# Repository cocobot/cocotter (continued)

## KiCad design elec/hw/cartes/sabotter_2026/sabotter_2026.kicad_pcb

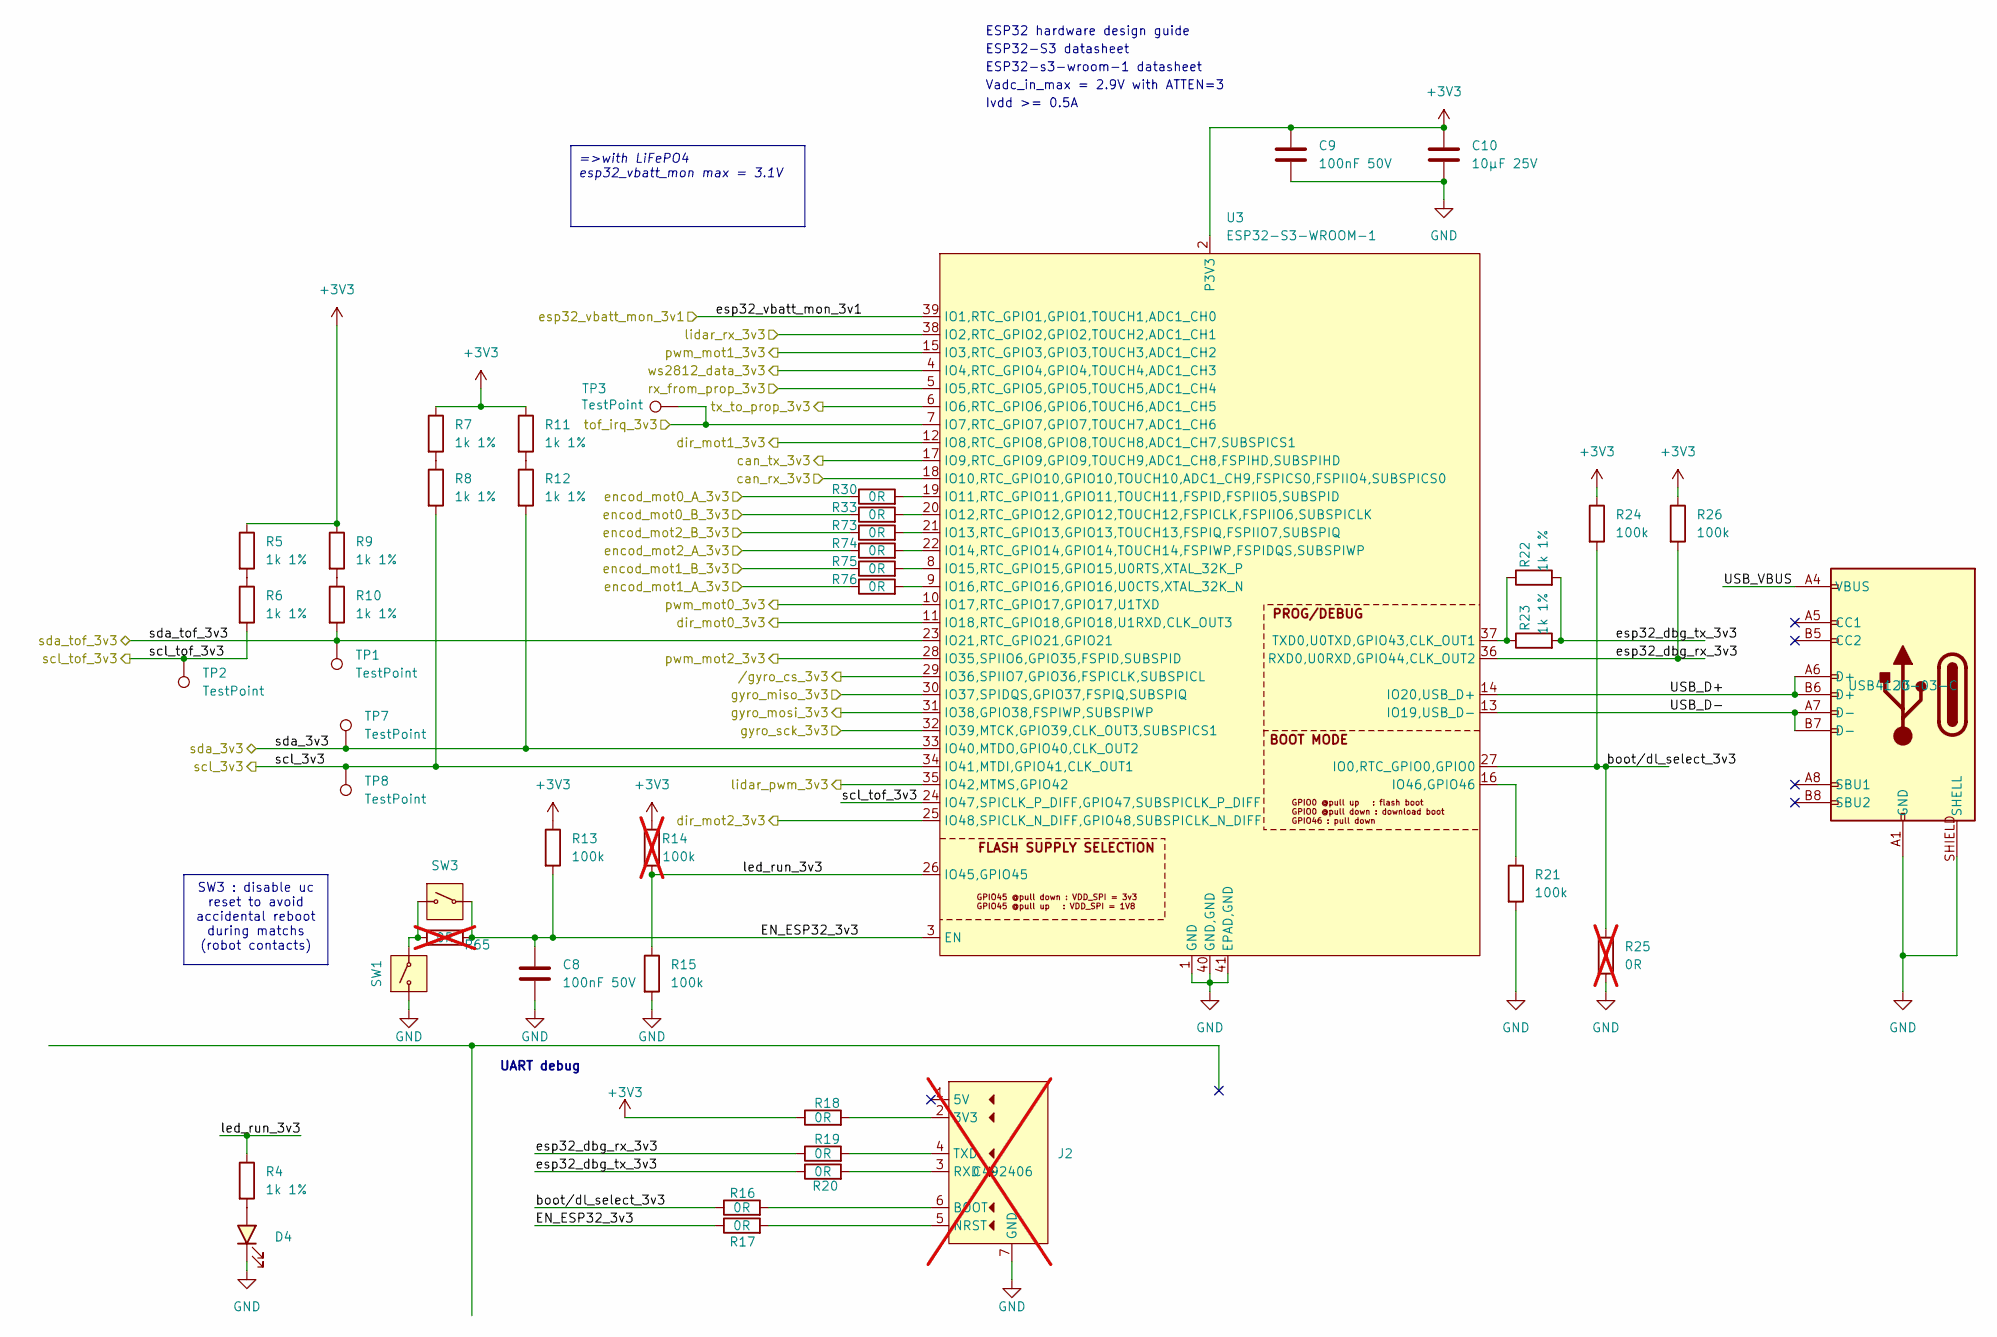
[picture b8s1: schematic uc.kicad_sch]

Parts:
C8, C9: 100nF 50V; C_0603_1608Metric; JLCPCB Part # C14663
C10: 10µF 25V; C_0805_2012Metric; JLCPCB Part # C15850
D4: green, 0603; LED_0603_1608Metric; DIGIKEY_REF 3147-B19Y1UYG-20C000313U1930CT-ND
J2: eps32_uart_programmer; JLCPCB Part # C492406; not fitted
J3: USB4120-03-C; JLCPCB Part # C7450621
R4, R5, R6, R7, R8, R9, R10, R11, R12, R22, R23: 1k 1%; r0603_reflow; mouser 603-RC0603FR-10100KL
R13, R15, R21, R24, R26: 100k; r0603_reflow; mouser 603-RC0603FR-10100KL
R14: 100k; r0603_reflow; mouser 603-RC0603FR-10100KL; not fitted
R16, R17, R18, R19, R20, R30, R33, R73, R74, R75, R76: 0R; r0603_reflow; JLCPCB Part # C431718
R25, R65: 0R; r0603_reflow; JLCPCB Part # C431718; not fitted
SW1: PTS525 SK15 SMTR2 LFS; PTS525; JLCPCB Part # C2689599
SW3: DSIC01LSGER; DIP_SW_SMD-1P; JLCPCB Part # C5370250
TP1, TP2, TP3, TP7, TP8: TestPoint; testpoint-THT-0.5mm
U3: ESP32-S3-WROOM-1; JLCPCB Part # C3013944

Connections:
+3V3: C9.1, C10.1, R5.1, R7.1, R9.1, R11.1, R13.1, R14.1, R18.1, R24.1, R26.1, U3.2 (P3V3); also elsewhere on the board
/interfaces/can_rx_3v3: U3.18 (IO10,RTC_GPIO10,GPIO10,TOUCH10,ADC1_CH9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); also elsewhere on the board
/interfaces/can_tx_3v3: U3.17 (IO9,RTC_GPIO9,GPIO9,TOUCH9,ADC1_CH8,FSP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); also elsewhere on the board
/interfaces/rx_from_prop_3v3: U3.5 (IO5,RTC_GPIO5,GPIO5,TOUCH5,ADC1_CH4); also elsewhere on the board
/interfaces/scl_3v3: R8.2, TP8.1, U3.34 (IO41,MTDI,GPIO41,CLK_OUT1); also elsewhere on the board
/interfaces/sda_3v3: R12.2, TP7.1, U3.33 (IO40,MTDO,GPIO40,CLK_OUT2); also elsewhere on the board
/interfaces/tx_to_prop_3v3: U3.6 (IO6,RTC_GPIO6,GPIO6,TOUCH6,ADC1_CH5); also elsewhere on the board
/interfaces/ws2812_data_3v3: U3.4 (IO4,RTC_GPIO4,GPIO4,TOUCH4,ADC1_CH3); also elsewhere on the board
/motors/DIR_MOT0_3V3: U3.11 (IO18,RTC_GPIO18,GPIO18,U1RXD,CLK_OUT3); also elsewhere on the board
/motors/DIR_MOT1_3V3: U3.12 (IO8,RTC_GPIO8,GPIO8,TOUCH8,ADC1_CH7,SUB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); also elsewhere on the board
/motors/DIR_MOT2_3V3: U3.25 (IO48,SPICLK_N_DIFF,GPIO48,SUBSPICLK_N_D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); also elsewhere on the board
/motors/ENCODER_A_MOT0_3V3: R30.1; also elsewhere on the board
/motors/ENCODER_A_MOT1_3V3: R76.1; also elsewhere on the board
/motors/ENCODER_A_MOT2_3V3: R74.1; also elsewhere on the board
/motors/ENCODER_B_MOT0_3V3: R33.1; also elsewhere on the board
/motors/ENCODER_B_MOT1_3V3: R75.1; also elsewhere on the board
/motors/ENCODER_B_MOT2_3V3: R73.1; also elsewhere on the board
/motors/PWM_MOT0_3V3: U3.10 (IO17,RTC_GPIO17,GPIO17,U1TXD); also elsewhere on the board
/motors/PWM_MOT1_3V3: U3.15 (IO3,RTC_GPIO3,GPIO3,TOUCH3,ADC1_CH2); also elsewhere on the board
/motors/PWM_MOT2_3V3: U3.28 (IO35,SPIIO6,GPIO35,FSPID,SUBSPID); also elsewhere on the board
/motors/tof_irq_3v3: TP3.1, U3.7 (IO7,RTC_GPIO7,GPIO7,TOUCH7,ADC1_CH6); also elsewhere on the board
/scl_tof_3v3: R6.2, TP2.1, U3.24 (IO47,SPICLK_P_DIFF,GPIO47,SUBSPICLK_P_D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); also elsewhere on the board
/sda_tof_3v3: R10.2, TP1.1, U3.23 (IO21,RTC_GPIO21,GPIO21); also elsewhere on the board
/sensors/gyro_miso_3v3: U3.30 (IO37,SPIDQS,GPIO37,FSPIQ,SUBSPIQ); also elsewhere on the board
/sensors/gyro_mosi_3v3: U3.31 (IO38,GPIO38,FSPIWP,SUBSPIWP); also elsewhere on the board
/sensors/gyro_sck_3v3: U3.32 (IO39,MTCK,GPIO39,CLK_OUT3,SUBSPICS1); also elsewhere on the board
/sensors/lidar_pwm_3v3: U3.35 (IO42,MTMS,GPIO42); also elsewhere on the board
/sensors/lidar_rx_3v3: U3.38 (IO2,RTC_GPIO2,GPIO2,TOUCH2,ADC1_CH1); also elsewhere on the board
/sensors//gyro_cs_3v3: U3.29 (IO36,SPIIO7,GPIO36,FSPICLK,SUBSPICL); also elsewhere on the board
/uc/EN_ESP32_3v3: C8.1, R13.2, R17.1, R65.2, SW3.2, U3.3 (EN)
/uc/USB_D+: J3.A6 (D+), J3.B6 (D+), U3.14 (IO20,USB_D+)
/uc/USB_D-: J3.A7 (D-), J3.B7 (D-), U3.13 (IO19,USB_D-)
/uc/USB_VBUS: J3.A4 (VBUS), J3.A9 (VBUS), J3.B4 (VBUS), J3.B9 (VBUS)
/uc/boot/dl_select_3v3: R16.1, R24.2, R25.1, U3.27 (IO0,RTC_GPIO0,GPIO0)
/uc/esp32_dbg_rx_3v3: R19.1, R26.2, U3.36 (RXD0,U0RXD,GPIO44,CLK_OUT2)
/uc/esp32_dbg_tx_3v3: R20.1, R22.2, R23.2
/uc/esp32_vbatt_mon_3v1: U3.39 (IO1,RTC_GPIO1,GPIO1,TOUCH1,ADC1_CH0); also elsewhere on the board
/uc/led_run_3v3: R4.1, R14.2, R15.1, U3.26 (IO45,GPIO45)
GND: C8.2, C9.2, C10.2, D4.C, J2.7 (GND), J3.A1 (GND), J3.A12 (GND), J3.B1 (GND), J3.B12 (GND), J3.SHIELD (SHELL), R15.2, R21.2, R25.2, SW1.A (1), U3.1 (GND), U3.40 (GND,GND), U3.41 (EPAD,GND); also elsewhere on the board
unnamed: D4.A, R4.2
unnamed: J2.2 (3V3), R18.2
unnamed: J2.6 (BOOT), R16.2
unnamed: J2.5 (NRST), R17.2
unnamed: J2.3 (RXD), R20.2
unnamed: J2.4 (TXD), R19.2
unnamed: R5.2, R6.1
unnamed: R7.2, R8.1
unnamed: R9.2, R10.1
unnamed: R11.2, R12.1
unnamed: R65.1, SW1.B (2), SW3.1
unnamed: R30.2, U3.19 (IO11,RTC_GPIO11,GPIO11,TOUCH11,FSPID,FS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)
unnamed: R33.2, U3.20 (IO12,RTC_GPIO12,GPIO12,TOUCH12,FSPICLK,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)
unnamed: R73.2, U3.21 (IO13,RTC_GPIO13,GPIO13,TOUCH13,FSPIQ,FS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)
unnamed: R74.2, U3.22 (IO14,RTC_GPIO14,GPIO14,TOUCH14,FSPIWP,F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)
unnamed: R75.2, U3.8 (IO15,RTC_GPIO15,GPIO15,U0RTS,XTAL_32K_P)
unnamed: R76.2, U3.9 (IO16,RTC_GPIO16,GPIO16,U0CTS,XTAL_32K_N)
unnamed: R21.1, U3.16 (IO46,GPIO46)
unnamed: R22.1, R23.1, U3.37 (TXD0,U0TXD,GPIO43,CLK_OUT1)

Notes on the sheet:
=>with LiFePO4 esp32_vbatt_mon max = 3.1V
SW3 : disable uc reset to avoid accidental reboot during matchs (robot contacts)
UART debug
ESP32-s3-wroom-1 datasheet
Ivdd >= 0.5A
ESP32 hardware design guide
Vadc_in_max = 2.9V with ATTEN=3
ESP32-S3 datasheet

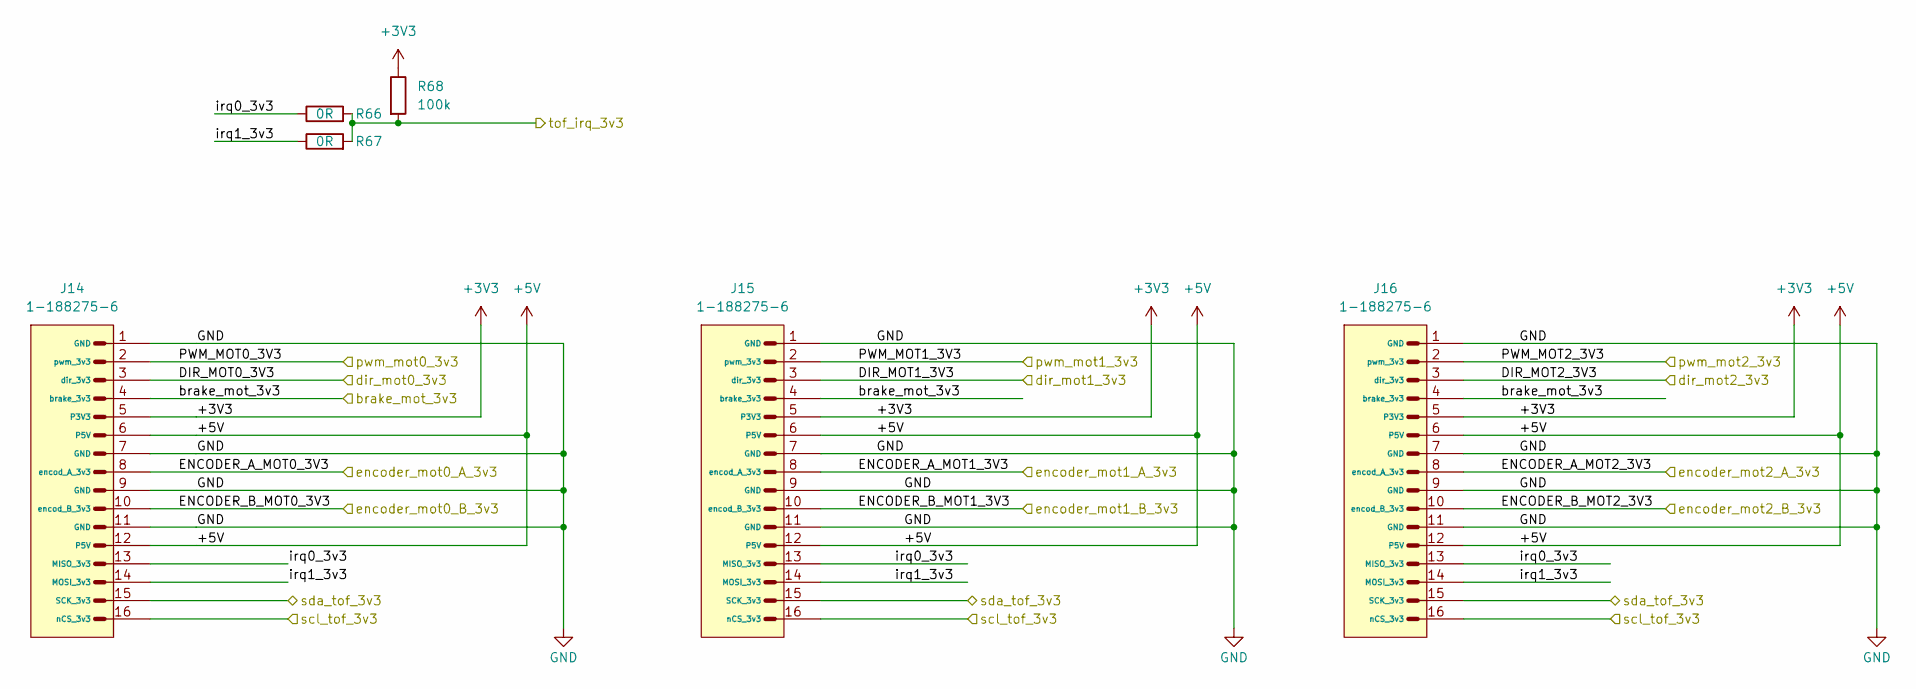
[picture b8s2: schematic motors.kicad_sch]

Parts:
J14, J15, J16: 1-188275-6; JLCPCB Part # C720217
R66, R67: 0R; r0603_reflow; JLCPCB Part # C431718
R68: 100k; r0603_reflow; mouser 603-RC0603FR-10100KL

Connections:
+3V3: J14.5 (P3V3), J15.5 (P3V3), J16.5 (P3V3), R68.1; also elsewhere on the board
+5V: J14.6 (P5V), J14.12 (P5V), J15.6 (P5V), J15.12 (P5V), J16.6 (P5V), J16.12 (P5V); also elsewhere on the board
/brake_mot_3v3: J14.4 (brake_3v3), J15.4 (brake_3v3), J16.4 (brake_3v3); also elsewhere on the board
/motors/DIR_MOT0_3V3: J14.3 (dir_3v3); also elsewhere on the board
/motors/DIR_MOT1_3V3: J15.3 (dir_3v3); also elsewhere on the board
/motors/DIR_MOT2_3V3: J16.3 (dir_3v3); also elsewhere on the board
/motors/ENCODER_A_MOT0_3V3: J14.8 (encod_A_3v3); also elsewhere on the board
/motors/ENCODER_A_MOT1_3V3: J15.8 (encod_A_3v3); also elsewhere on the board
/motors/ENCODER_A_MOT2_3V3: J16.8 (encod_A_3v3); also elsewhere on the board
/motors/ENCODER_B_MOT0_3V3: J14.10 (encod_B_3v3); also elsewhere on the board
/motors/ENCODER_B_MOT1_3V3: J15.10 (encod_B_3v3); also elsewhere on the board
/motors/ENCODER_B_MOT2_3V3: J16.10 (encod_B_3v3); also elsewhere on the board
/motors/PWM_MOT0_3V3: J14.2 (pwm_3v3); also elsewhere on the board
/motors/PWM_MOT1_3V3: J15.2 (pwm_3v3); also elsewhere on the board
/motors/PWM_MOT2_3V3: J16.2 (pwm_3v3); also elsewhere on the board
/motors/irq0_3v3: J14.13 (MISO_3v3), J15.13 (MISO_3v3), J16.13 (MISO_3v3), R66.1
/motors/irq1_3v3: J14.14 (MOSI_3v3), J15.14 (MOSI_3v3), J16.14 (MOSI_3v3), R67.1
/motors/tof_irq_3v3: R66.2, R67.2, R68.2; also elsewhere on the board
/scl_tof_3v3: J14.16 (nCS_3v3), J15.16 (nCS_3v3), J16.16 (nCS_3v3); also elsewhere on the board
/sda_tof_3v3: J14.15 (SCK_3v3), J15.15 (SCK_3v3), J16.15 (SCK_3v3); also elsewhere on the board
GND: J14.1 (GND), J14.7 (GND), J14.9 (GND), J14.11 (GND), J15.1 (GND), J15.7 (GND), J15.9 (GND), J15.11 (GND), J16.1 (GND), J16.7 (GND), J16.9 (GND), J16.11 (GND); also elsewhere on the board

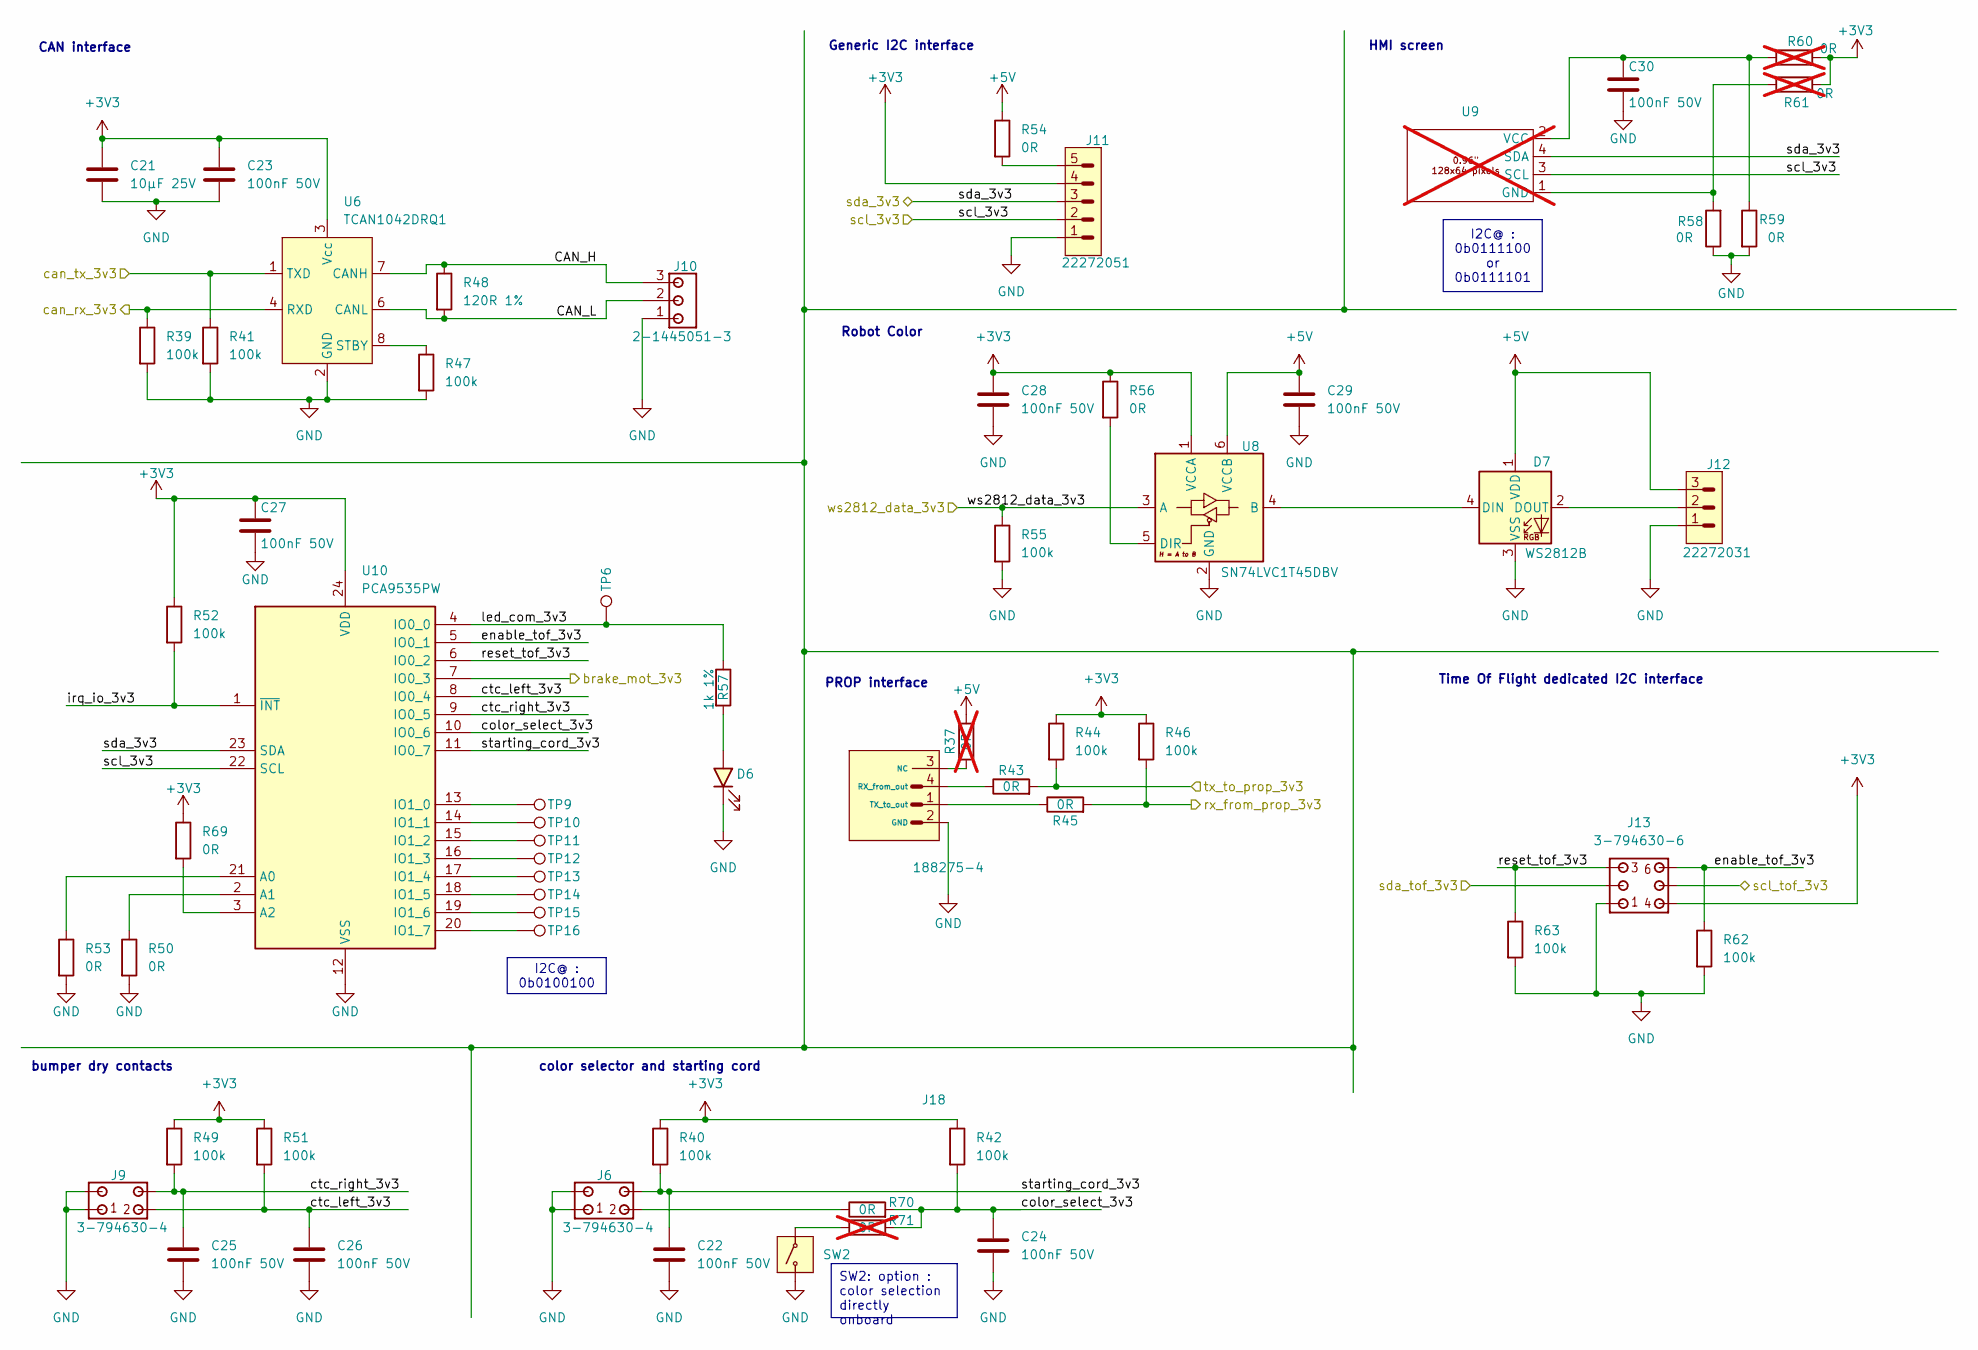
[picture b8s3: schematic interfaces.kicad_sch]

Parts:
C21: 10µF 25V; C_0805_2012Metric; JLCPCB Part # C15850
C22, C23, C24, C25, C26, C27, C28, C29, C30: 100nF 50V; C_0603_1608Metric; JLCPCB Part # C14663
D6: green, 0603; LED_0603_1608Metric; DIGIKEY_REF 3147-B19Y1UYG-20C000313U1930CT-ND
D7: WS2812B; LED_WS2812B_PLCC4_5.0x5.0mm_P3.2mm; JLCPCB Part # C2843785
J6, J9: 3-794630-4; JLCPCB Part # C5164688
J10: 2-1445051-3; JLCPCB Part # C17473329
J11: 22272051; JLCPCB Part # C585785
J12: 22272031; JLCPCB Part # C471416
J13: 3-794630-6; JLCPCB Part # C305795
J18: 188275-4; JLCPCB Part # C720206
R37, R60, R61, R71: 0R; r0603_reflow; JLCPCB Part # C431718; not fitted
R39, R40, R41, R42, R44, R46, R47, R49, R51, R52, R55, R62, R63: 100k; r0603_reflow; mouser 603-RC0603FR-10100KL
R43, R45, R50, R53, R54, R56, R58, R59, R69, R70: 0R; r0603_reflow; JLCPCB Part # C431718
R48: 120R 1%; r1206_reflow; JLCPCB Part # C17909
R57: 1k 1%; r0603_reflow; mouser 603-RC0603FR-10100KL
SW2: DSIC01LSGER; DIP_SW_SMD-1P; JLCPCB Part # C5370250
TP6, TP9, TP10, TP11, TP12, TP13, TP14, TP15, TP16: TestPoint; testpoint-THT-0.5mm
U6: TCAN1042DRQ1; D0008A; JLCPCB Part # C118837
U8: SN74LVC1T45DBV; SOT-23-6; JLCPCB Part # C7843
U9: OLED_0.96inch; not fitted
U10: PCA9535PW; TSSOP-24_4.4x7.8mm_P0.65mm; JLCPCB Part # C42420616

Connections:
+3V3: C21.1, C23.1, C27.1, C28.1, J11.4, J13.4, R40.1, R42.1, R44.1, R46.1, R49.1, R51.1, R52.1, R56.1, R60.2, R61.2, R69.1, U6.3 (Vcc), U8.1 (VCCA), U10.24 (VDD); also elsewhere on the board
+5V: C29.1, D7.1 (VDD), J12.3, R37.2, R54.1, U8.6 (VCCB); also elsewhere on the board
/brake_mot_3v3: U10.7 (IO0_3); also elsewhere on the board
/interfaces/CAN_H: J10.3, R48.1, U6.7 (CANH)
/interfaces/CAN_L: J10.2, R48.2, U6.6 (CANL)
/interfaces/can_rx_3v3: R39.1, U6.4 (RXD); also elsewhere on the board
/interfaces/can_tx_3v3: R41.1, U6.1 (TXD); also elsewhere on the board
/interfaces/color_select_3v3: C24.1, R42.2, R70.2, R71.2, U10.10 (IO0_6)
/interfaces/ctc_left_3v3: C26.1, J9.2, R51.2, U10.8 (IO0_4)
/interfaces/ctc_right_3v3: C25.1, J9.4, R49.2, U10.9 (IO0_5)
/interfaces/enable_tof_3v3: J13.6, R62.1, U10.5 (IO0_1)
/interfaces/irq_io_3v3: R52.2, U10.1 (~INT)
/interfaces/led_com_3v3: R57.1, TP6.1, U10.4 (IO0_0)
/interfaces/reset_tof_3v3: J13.3, R63.1, U10.6 (IO0_2)
/interfaces/rx_from_prop_3v3: R45.2, R46.2; also elsewhere on the board
/interfaces/scl_3v3: J11.2, U9.3 (SCL), U10.22 (SCL); also elsewhere on the board
/interfaces/sda_3v3: J11.3, U9.4 (SDA), U10.23 (SDA); also elsewhere on the board
/interfaces/starting_cord_3v3: C22.1, J6.4, R40.2, U10.11 (IO0_7)
/interfaces/tx_to_prop_3v3: R43.2, R44.2; also elsewhere on the board
/interfaces/ws2812_data_3v3: R55.1, U8.3 (A); also elsewhere on the board
/scl_tof_3v3: J13.5; also elsewhere on the board
/sda_tof_3v3: J13.2; also elsewhere on the board
GND: C21.2, C22.2, C23.2, C24.2, C25.2, C26.2, C27.2, C28.2, C29.2, C30.2, D6.C, D7.3 (VSS), J6.1, J6.3, J9.1, J9.3, J10.1, J11.1, J12.1, J13.1, J18.2 (GND), R39.2, R41.2, R47.2, R50.2, R53.2, R55.2, R58.1, R59.2, R62.2, R63.2, SW2.1, U6.2 (GND), U8.2 (GND), U10.12 (VSS); also elsewhere on the board
unnamed: D6.A, R57.2
unnamed: D7.4 (DIN), U8.4 (B)
unnamed: D7.2 (DOUT), J12.2
unnamed: J6.2, R70.1
unnamed: J11.5, R54.2
unnamed: J18.3 (NC), R37.1
unnamed: J18.4 (RX_from_out), R43.1
unnamed: J18.1 (TX_to_out), R45.1
unnamed: R71.1, SW2.2
unnamed: R47.1, U6.8 (STBY)
unnamed: R56.2, U8.5 (DIR)
unnamed: R58.2, R61.1, U9.1 (GND)
unnamed: C30.1, R59.1, R60.1, U9.2 (VCC)
unnamed: R53.1, U10.21 (A0)
unnamed: R50.1, U10.2 (A1)
unnamed: R69.2, U10.3 (A2)
unnamed: TP9.1, U10.13 (IO1_0)
unnamed: TP10.1, U10.14 (IO1_1)
unnamed: TP11.1, U10.15 (IO1_2)
unnamed: TP12.1, U10.16 (IO1_3)
unnamed: TP13.1, U10.17 (IO1_4)
unnamed: TP14.1, U10.18 (IO1_5)
unnamed: TP15.1, U10.19 (IO1_6)
unnamed: TP16.1, U10.20 (IO1_7)

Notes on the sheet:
I2C@ : 0b0111100 or 0b0111101
SW2: option : color selection directly onboard
I2C@ : 0b0100100
CAN interface
Robot Color
HMI screen
PROP interface
bumper dry contacts
Generic I2C interface
color selector and starting cord
Time Of Flight dedicated I2C interface

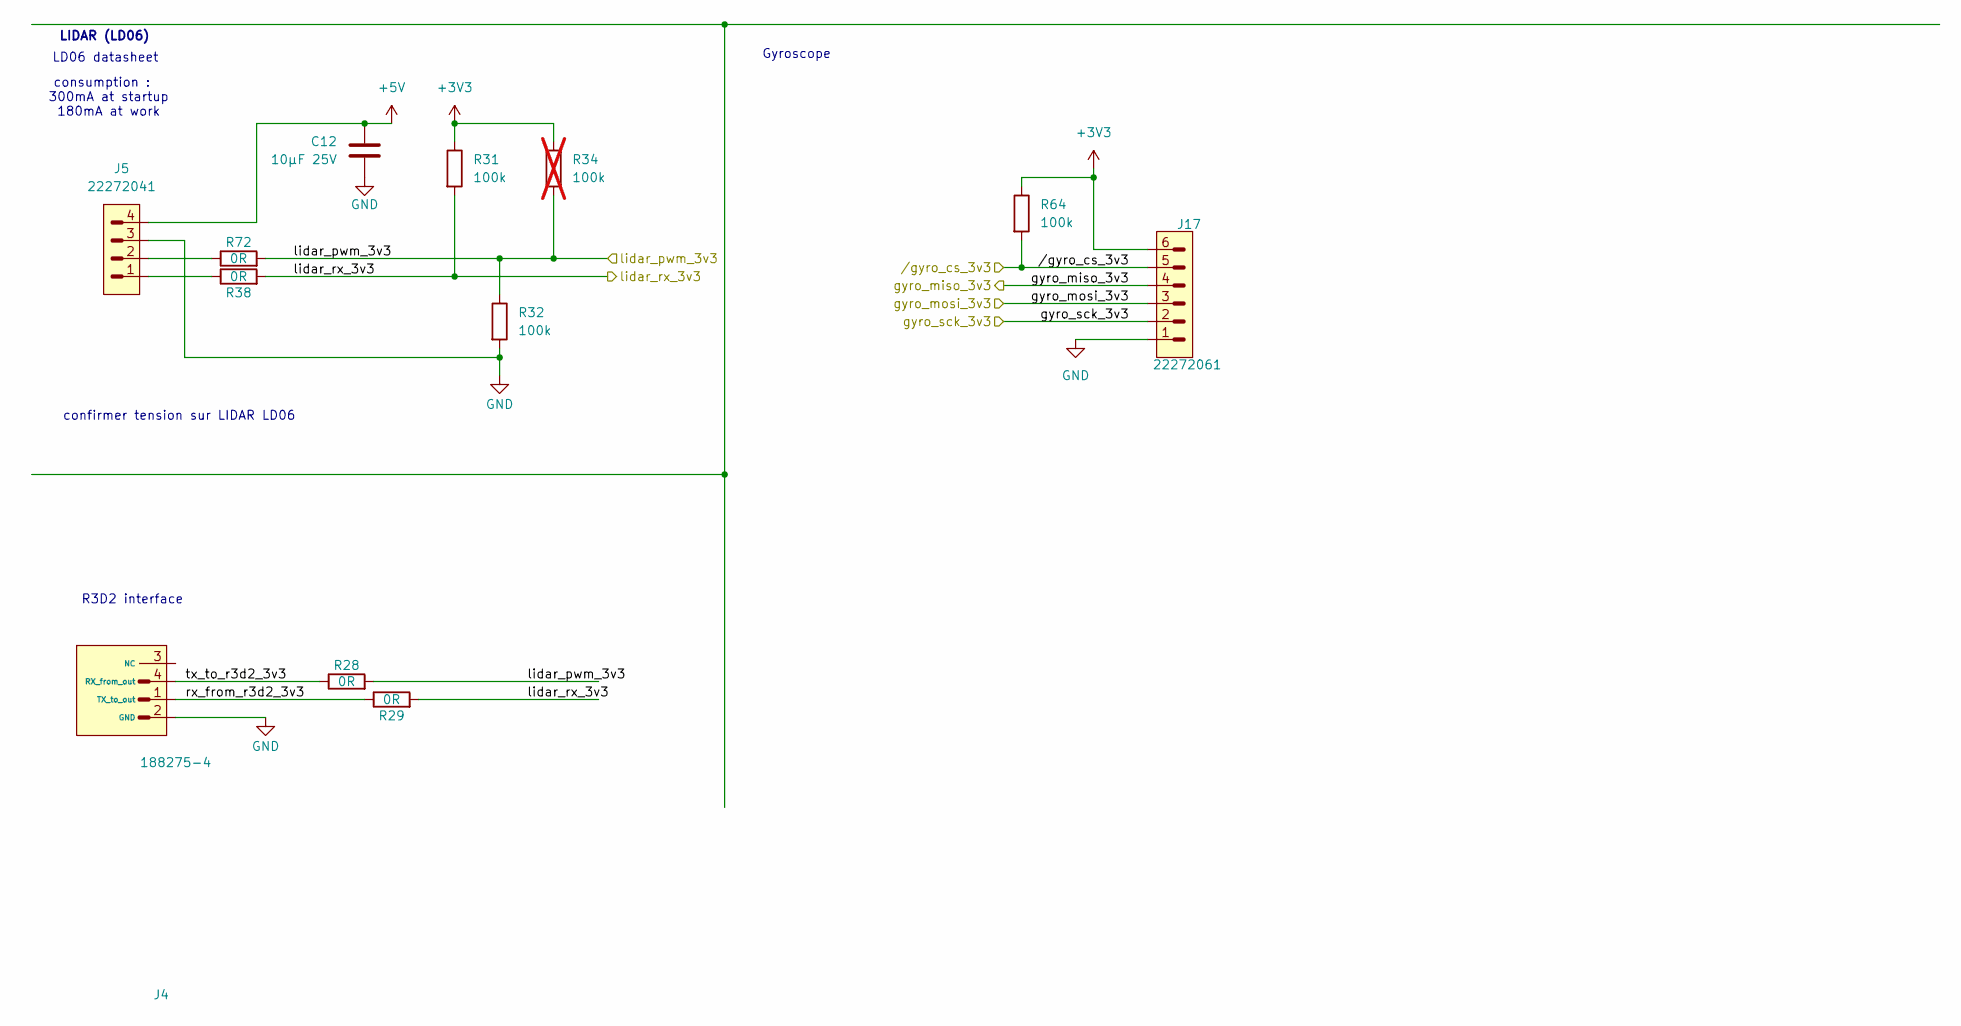
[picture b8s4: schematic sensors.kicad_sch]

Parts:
C12: 10µF 25V; C_0805_2012Metric; JLCPCB Part # C15850
J4: 188275-4; JLCPCB Part # C720206
J5: 22272041; JLCPCB Part # C504991
J17: 22272061; JLCPCB Part # C504992
R28, R29, R38, R72: 0R; r0603_reflow; JLCPCB Part # C431718
R31, R32, R64: 100k; r0603_reflow; mouser 603-RC0603FR-10100KL
R34: 100k; r0603_reflow; mouser 603-RC0603FR-10100KL; not fitted

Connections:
+3V3: J17.6, R31.1, R34.1, R64.1; also elsewhere on the board
+5V: C12.1, J5.4; also elsewhere on the board
/sensors/gyro_miso_3v3: J17.4; also elsewhere on the board
/sensors/gyro_mosi_3v3: J17.3; also elsewhere on the board
/sensors/gyro_sck_3v3: J17.2; also elsewhere on the board
/sensors/lidar_pwm_3v3: R28.2, R32.1, R34.2, R72.2; also elsewhere on the board
/sensors/lidar_rx_3v3: R29.2, R31.2, R38.2; also elsewhere on the board
/sensors/rx_from_r3d2_3v3: J4.1 (TX_to_out), R29.1
/sensors/tx_to_r3d2_3v3: J4.4 (RX_from_out), R28.1
/sensors//gyro_cs_3v3: J17.5, R64.2; also elsewhere on the board
GND: C12.2, J4.2 (GND), J5.3, J17.1, R32.2; also elsewhere on the board
unnamed: J5.1, R38.1
unnamed: J5.2, R72.1

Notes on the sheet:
R3D2 interface
consumption : 300mA at startup 180mA at work
LIDAR (LD06)
Gyroscope
LD06 datasheet
confirmer tension sur LIDAR LD06

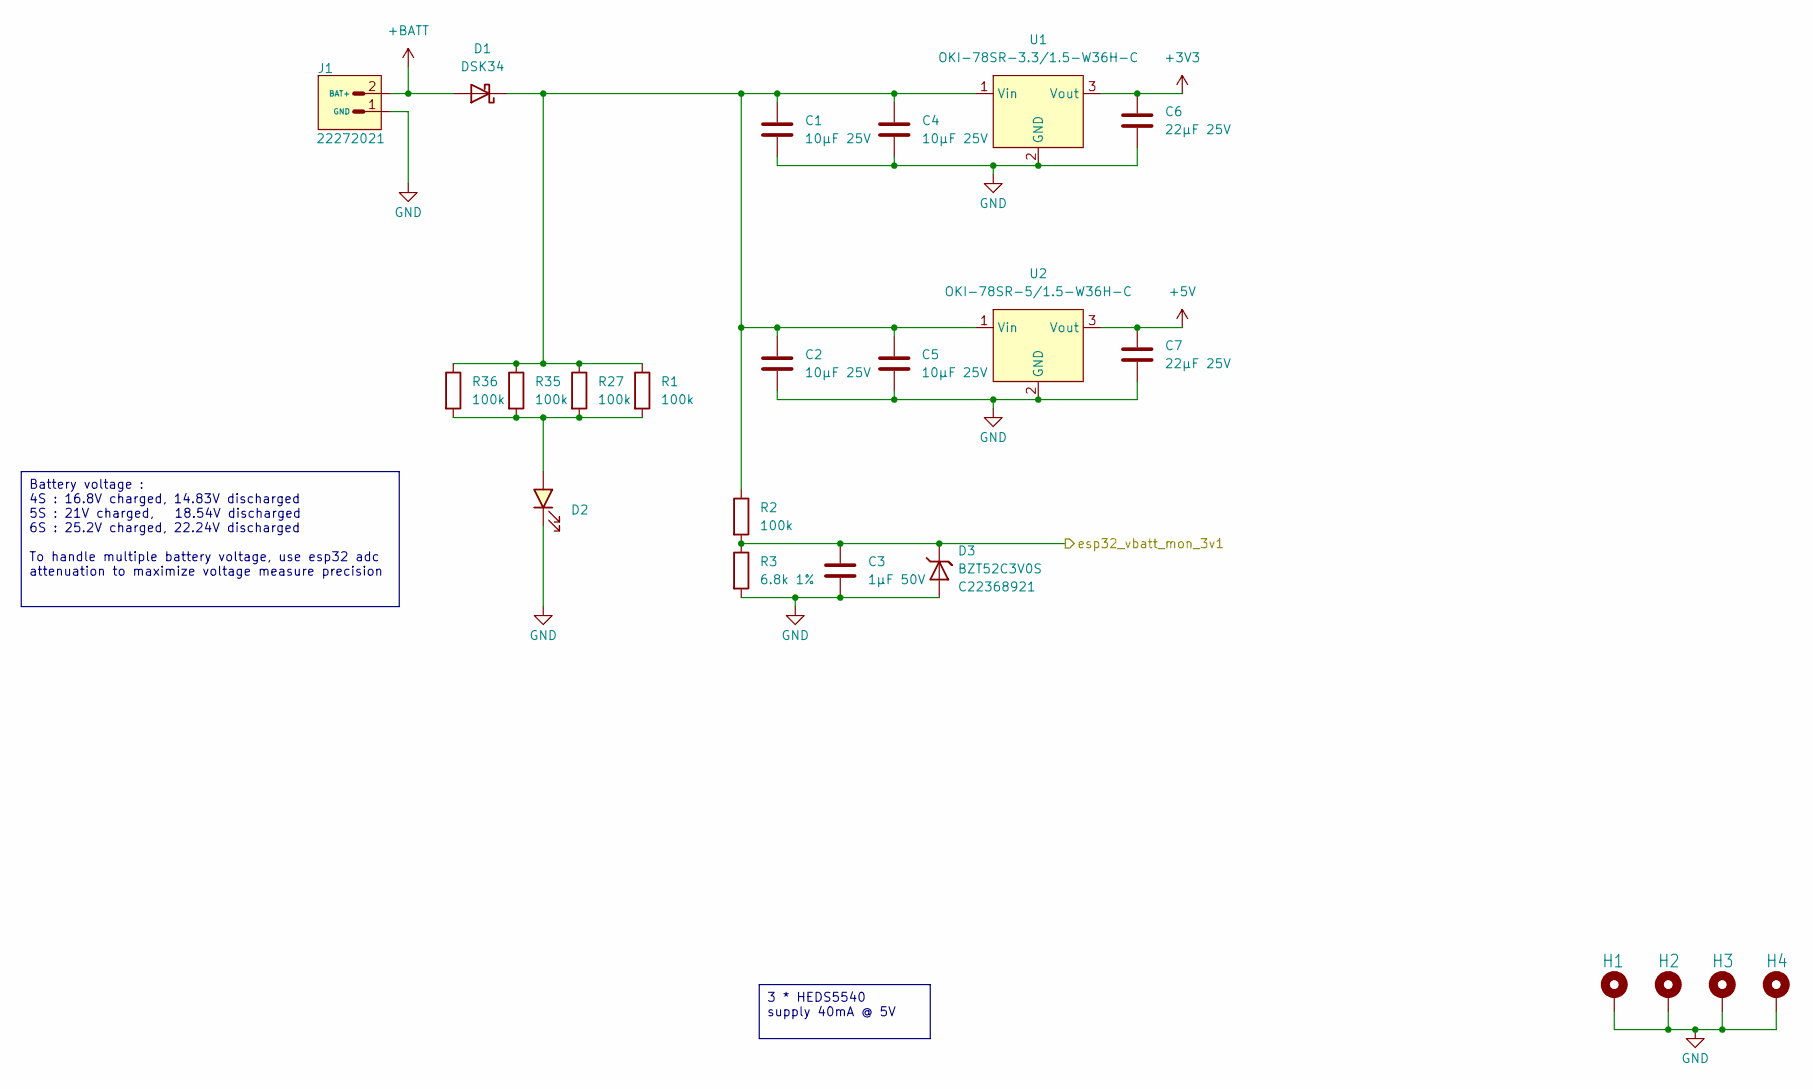
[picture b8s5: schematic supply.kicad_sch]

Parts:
C1, C2, C4, C5: 10µF 25V; C_0805_2012Metric; JLCPCB Part # C15850
C3: 1µF 50V; C_0805_2012Metric; JLCPCB Part # C28323
C6, C7: 22µF 25V; C_1206_3216Metric; JLCPCB Part # C2918511
D1: DSK34; D_SOD-123; JLCPCB Part # C727076
D2: green, 0603; LED_0603_1608Metric; DIGIKEY_REF 3147-B19Y1UYG-20C000313U1930CT-ND
D3: BZT52C3V0S; SOD-323; JLCPCB Part # C22368921
H1, H2, H3, H4: MOUNT-PAD-ROUND3.3; MountingHole_3.2mm_M3_Pad_Via
J1: 22272021; JLCPCB Part # C293316
R1, R2, R27, R35, R36: 100k; r0603_reflow; mouser 603-RC0603FR-10100KL
R3: 6.8k 1%; r0603_reflow; JLCPCB Part # C23212
U1: OKI-78SR-3.3/1.5-W36H-C; OKI78SR-H
U2: OKI-78SR-5/1.5-W36H-C; OKI78SR-H

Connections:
+3V3: C6.1, U1.3 (Vout); also elsewhere on the board
+5V: C7.1, U2.3 (Vout); also elsewhere on the board
+BATT: D1.2 (A), J1.2 (BAT+)
/uc/esp32_vbatt_mon_3v1: C3.1, D3.1 (K), R2.2, R3.1; also elsewhere on the board
GND: C1.2, C2.2, C3.2, C4.2, C5.2, C6.2, C7.2, D2.C, D3.2 (A), H1.1, H2.1, H3.1, H4.1, J1.1 (GND), R3.2, U1.2 (GND), U2.2 (GND); also elsewhere on the board
unnamed: C1.1, C2.1, C4.1, C5.1, D1.1 (K), R1.1, R2.1, R27.1, R35.1, R36.1, U1.1 (Vin), U2.1 (Vin)
unnamed: D2.A, R1.2, R27.2, R35.2, R36.2

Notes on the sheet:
3 * HEDS5540 supply 40mA @ 5V
Battery voltage : 4S : 16.8V charged, 14.83V discharged 5S : 21V charged, 18.54V discharged 6S : 25.2V charged, 22.24V discharged To handle multiple battery voltage, use esp32 adc attenuation to maximize voltage measure precision

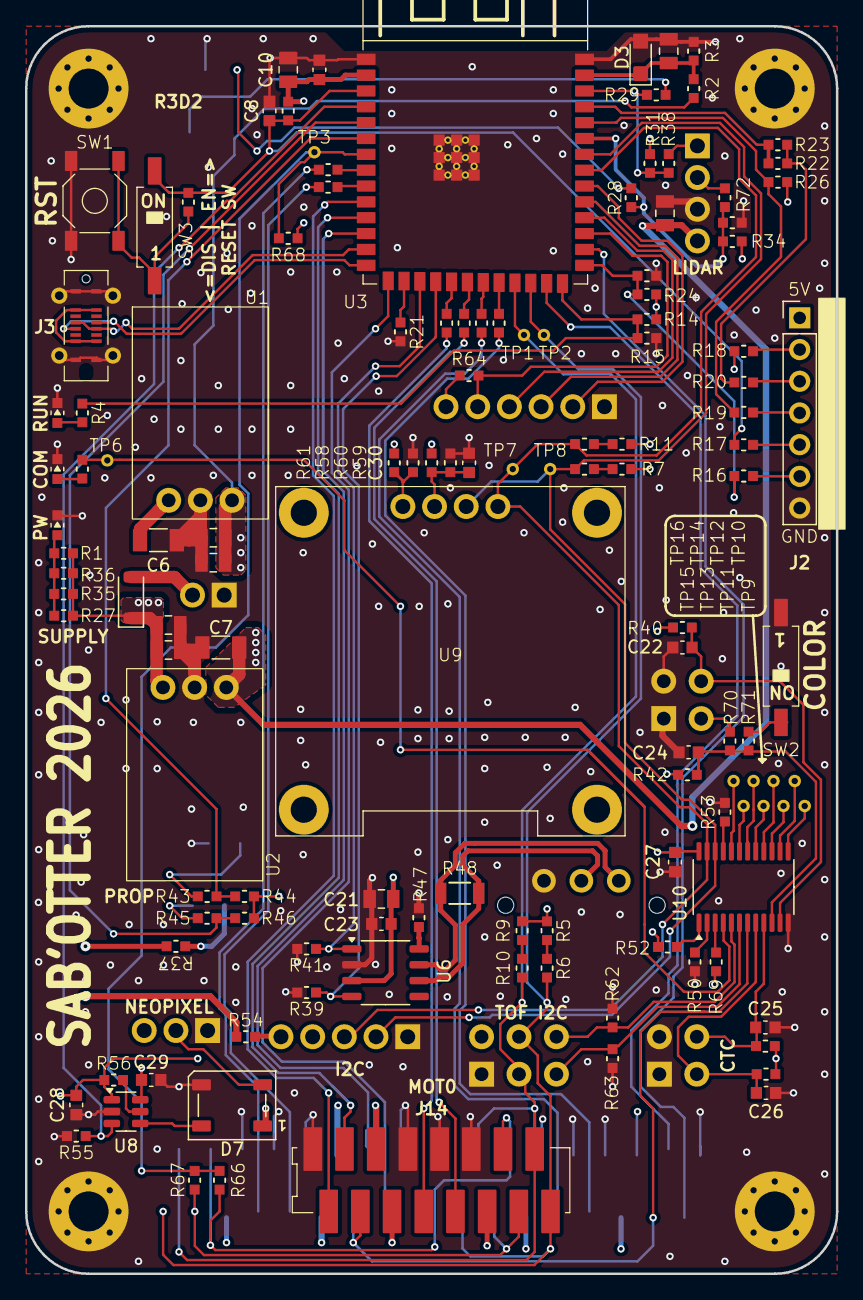
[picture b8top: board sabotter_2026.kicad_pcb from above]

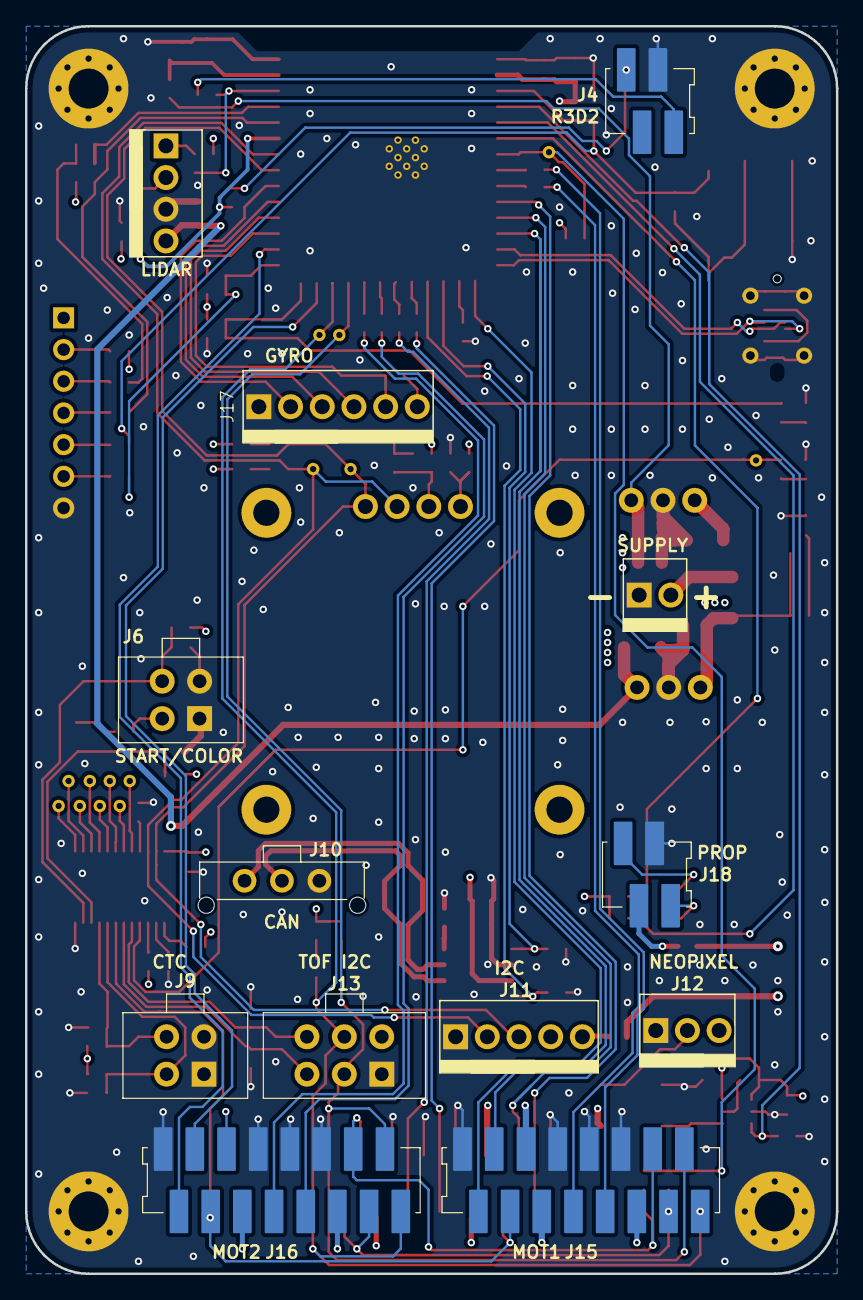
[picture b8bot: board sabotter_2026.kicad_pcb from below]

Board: 4 copper layers, 65.0 x 100.0 mm, 147 parts (13 on the bottom side), 103 nets.
